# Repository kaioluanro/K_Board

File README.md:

# K_Board

Project 65% keyboard RGB custom, based in the QMK Firmware with uma display.

## Note

Project in development

## Features Hardware

- 256 GPIO digitais.
- Rotery Encode Switch.
- Display, Show menu options.

## Licença

[GPL3](https://choosealicense.com/licenses/gpl-3.0/)

## Autores

- [@kaioluanro](https://github.com/kaioluanro)

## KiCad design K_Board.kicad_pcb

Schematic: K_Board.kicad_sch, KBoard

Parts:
C1, C2, C3, C4, C10, C15, C16, C17, C18, C19, C20, C21, C22, C23, C24, C25, C26, C27, C28, C29, C30, C31, C32, C33, C34, C35, C36, C37, C38, C39, C40, C41, C42, C43, C44, C45, C46, C47, C48, C49, C50, C51, C52, C53, C54, C55, C56, C57, C58, C59, C60, C61, C62, C63, C64, C65, C66, C67, C68, C69, C70, C71, C72, C73, C74, C75, C76, C77, C78, C79, C80, C81, C82, C83, C84, C85, C86, C87, C88, C89, C90, C91, C102, C103, C104, C105, C106, C107, C108, C109, C110, C111, C112, C113, C114, C115, C116: 100n; C_0402_1005Metric; Manufacturer Part Number 0402F104Z160CT
C5: 10u; CP_EIA-3216-10_Kemet-I_Pad1.58x1.35mm_HandSolder; Manufacturer Part Number TAJA106K016RNJ
C6, C12, C14: 1u; C_0201_0603Metric; Manufacturer Part Number UMK107AB7105KA-T
C7: 10n; C_0402_1005Metric
C8, C9: 8p; C_0402_1005Metric
C11: 4.7u; C_0402_1005Metric
C13, C92, C97: 10u; C_0402_1005Metric; Manufacturer Part Number UMK325AB7106KM-T
C93: 15u; C_0402_1005Metric; Manufacturer Part Number UMK325AB7106KM-T
C94, C95, C99, C100: 1u; C_0805_2012Metric; Manufacturer Part Number CC0805KKX7R7BB105
C96: 2.2u; C_1206_3216Metric
C98: 4.7u; C_1206_3216Metric
C101: 0.1u; C_1206_3216Metric
D1, D7, D13, D19, D24, D29, D34, D40, D45, D50, D55, D61, D67, D70, D71, D83, D85, D86, D87, D88, D89, D90, D91, D92, D93, D94, D95, D96, D97, D98, D99, D100, D101, D102, D103, D104, D105, D106, D107, D108, D109, D110, D111, D112, D113, D114, D115, D116, D117, D118, D119, D120, D121, D122, D123, D124, D125, D126, D127, D128, D129, D130, D131, D132, D133, D134, D135, D136, D137, D138, D139, D140, D141, D162, D163, D164, D165, D166, D167, D168, D169, D170, D171, D172, D173, D174, D175, D176: WS2812B-Mini; LED_SK6812MINI_PLCC4_3.5x3.5mm_P1.75mm; Manufacturer Part Number WS2812B-Mini
D2, D3, D4, D5, D6, D8, D9, D10, D11, D12, D14, D15, D16, D17, D18, D20, D21, D22, D23, D25, D26, D27, D28, D30, D31, D32, D33, D35, D36, D37, D38, D39, D41, D42, D43, D44, D46, D47, D48, D49, D51, D52, D53, D54, D56, D57, D58, D59, D60, D62, D63, D64, D65, D66, D68, D69, D72, D73, D74, D75, D76, D77, D78, D79, D80, D81, D82, D142, D143, D146, D147, D148, D149, D150, D151, D152, D153, D154, D155, D156, D157, D158, D159, D160, D161: 1N4148W; D_SOD-123; Manufacturer Part Number 1N4148W
D84: ZRE B5819W-SL; D_SOD-123; Manufacturer Part Number B5819W-SL
D144, D145: 1N4148W; D_SOD-123
F1: mSMD110-16V; C_1812_4532Metric; Manufacturer Part Number mSMD110-16V
FB1: CBW201209U121T; L_0805_2012Metric; Manufacturer Part Number CBW201209U121T
J1: TYPE-C-31-M-12; USB_C_Receptacle_Hroparts_TYPE-C-31-M-12; Manufacturer Part Number TYPE-C-31-M-12
J2: Conn_01x04; PinHeader_1x4_P2.54mm_Angled
J3: Conns_I2C; SC-74-6_1.5x2.9mm_P0.95mm
J4: Conn_02x18_Counter_Clockwise; SMDIP-18_W7.62mm
J5: USB pins; PinHeader_1x4_P2.54mm_Angled
LED1, LED2, LED3, LED4, LED5, LED6, LED7, LED8, LED9, LED10: LED; LED_THT_2.54mm
Q1: 2N7002; SOT-23; Manufacturer Part Number 2N7002
Q2: AO3401A; SOT-23; Manufacturer Part Number Alpha & Omega Semicon
Q3, Q4: 2N7002; SOT-23
R1, R2: 4.7k; R_0402_1005Metric
R3, R55: 10k; R_0805_2012Metric
R4, R10, R11, R12, R13, R14, R15, R16, R17, R18, R19, R20, R21, R22, R23, R24, R25, R26, R27, R28, R29, R30, R31, R32, R33, R34, R35, R36, R37, R38, R39, R40, R41, R42, R43, R44, R45, R47, R48, R49, R50, R51, R52, R53, R54, R56, R57, R58, R59, R60, R61, R62, R63, R64, R65, R66, R67, R68, R69, R70, R71, R72, R73, R74, R75, R76, R77, R78, R79, R80, R81, R82, R83, R112, R113, R114, R115, R116, R117, R118, R119, R120, R121, R122, R123, R124, R125, R126: 5.1R; R_0805_2012Metric
R5: 0R; R_0402_1005Metric
R6, R7: 100k; R_0805_2012Metric
R8, R9: 5.1k; R_0805_2012Metric
R46: 1.5k; R_0402_1005Metric
R84, R85, R101, R102, R103, R104, R105: 4.7k; R_0805_2012Metric
R86, R87, R89, R90, R93, R94, R96, R97, R98, R99: 1k; R_0805_2012Metric; Manufacturer Part Number 0805W8F1001T5E
R88, R95: 100R; R_0402_1005Metric; Manufacturer Part Number 0402WGF1000TCE
R91, R92: 10k; R_0402_1005Metric; Manufacturer Part Number 0402WGF1002TCE
R100: 530k; R_0805_2012Metric
R106, R108, R110: 100R; R_0402_1005Metric
R107: 330k; R_0402_1005Metric
R109: 1M; R_0402_1005Metric
R111: 10K; R_0402_1005Metric
SW1: EC11E1544407; RotaryEncoder_Alps_EC11E-Switch_Vertical_H20mm; Manufacturer Part Number EC11E1544407
SW2, SW8, SW9, SW10, SW11, SW14, SW15, SW16, SW17, SW19, SW20, SW21, SW22, SW23, SW24, SW25, SW26, SW27, SW28, SW29, SW30, SW31, SW32, SW33, SW34, SW35, SW36, SW37, SW38, SW40, SW41, SW42, SW43, SW44, SW45, SW46, SW47, SW48, SW49, SW50, SW51, SW52, SW53, SW54, SW55, SW56, SW57, SW58, SW59, SW60, SW61, SW62, SW63, SW64, SW65, SW66, SW67, SW68, SW69, SW70, SW71, SW72, SW74, SW76, SW77, SW78, SW79, SW80, SW81, SW82, SW83, SW84: Mechanical_Switch; MX100
SW3: Mechanical_Switch; MX150
SW4, SW75: Mechanical_Switch; MX175
SW5, SW6, SW12, SW18: Mechanical_Switch; MX125
SW7: Mechanical_Switch; MX225
SW13: K2-1187SQ-A4SW-06; Manufacturer Part Number K2-1187SQ-A4SW-06
SW39: Mechanical_Switch; MX625R
SW73, SW85, SW86: Mechanical_Switch; MX200
U1: AT24C256C-SSHL-T; SOIC-8; Manufacturer Part Number AT24C256C-SSHL-T
U2: STM32F411CEU6; STM_UFQFPN-48_LQFP-48-1EP_7x7mm_P0.5mm_HandSoldering_Therma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; Manufacturer Part Number STM32F411
U3: SGM2007-3.3XN5/TR; SOT-23-5; Manufacturer Part Number SGM2007-3.3XN5/TR
U4: TXS0101DCKR; SOT-363_SC-70-6; Manufacturer Part Number TXS0101DCKR
U5, U6: PCF8575; VQFN-24-1EP_4x4mm_P0.5mm_EP2.45x2.45mm_ThermalVias
U7: 0.96'_display_OLED; 0.96 OLED Display
U8: USBLC6-2SC6; SOT-23-6; Manufacturer Part Number USBLC6-2SC6; LCSC Part Number C7519
X1: X6521WR-2x05H-C30D60; PinHeader_2x5_P2.54mm_Vertical_Staggered; Manufacturer Part Number X6521WR-2x05H-C30D60
X2: Conn_01x03; PinHeader_1x3_P2.54mm_Vertical
Y1: X1E0000210621; Crystal_SMD_3225-4Pin_3.2x2.5mm; Manufacturer Part Number 25MHz SMD Crystal Resonator 9pF 40Ω ±10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

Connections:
3V3: C1.2, C2.1, C3.1, C4.2, C5.1, C6.1, C7.1, C10.2, C14.1, C62.1, C94.2, C95.2, D84.2 (A), D144.1 (K), J2.2, J2.3, J2.4, J3.3, J3.4, J3.5, J3.6, R1.1, R2.1, R7.1, R46.1, R55.1, R84.1, R85.1, R101.2, R102.1, R103.1, R104.1, R105.1, SW13.1 (A), U1.8 (VCC), U2.1 (VBAT), U2.9 (VDDA/VREF+), U2.21 (B10), U2.24 (VDD), U2.29 (PA8), U2.36 (VDD), U2.39 (PB3), U2.40 (PB4), U2.48 (VDD), U3.5 (OUT), U4.1 (VCCA), U5.24 (VCC), U6.21 (A0), U6.24 (VCC), U7.5 (VCC), U7.8 (VCC), X1.7, X1.8
5V: C12.1, C63.2, D84.1 (K), F1.2, J5.1, Q2.2 (S), R4.2, R6.1, R10.2, R11.2, R12.2, R13.2, R14.2, R15.2, R16.2, R17.2, R18.2, R19.2, R20.2, R21.2, R22.2, R23.2, R24.2, R25.2, R26.2, R27.2, R28.2, R29.2, R30.2, R31.2, R32.2, R33.2, R34.2, R35.2, R36.2, R37.2, R38.2, R39.2, R40.2, R41.2, R42.2, R43.2, R44.2, R45.2, R47.2, R48.2, R49.2, R50.2, R51.2, R52.2, R53.2, R54.2, R56.2, R57.2, R58.2, R59.2, R60.2, R61.2, R62.2, R63.2, R64.2, R65.2, R66.2, R67.2, R68.2, R69.2, R70.2, R71.2, R72.2, R73.2, R74.2, R75.2, R76.2, R77.2, R78.2, R79.2, R80.2, R81.2, R82.2, R83.2, R92.2, R112.2, R113.2, R114.2, R115.2, R116.2, R117.2, R118.2, R119.2, R120.2, R121.2, R122.2, R123.2, R124.2, R125.2, R126.2, U3.1 (IN), U3.3 (EN), U4.6 (VCCB), X2.1; also elsewhere on the board
BACKLIGHT_3V3: R88.1, U2.16 (PA6)
BOOT0: C92.1, R107.2, R109.1, R111.2, U2.44 (BOOT0), X1.5
C1: SW2.1, SW3.1, SW4.1, SW5.1, SW6.1, SW19.1, U5.4 (P0)
C2: SW8.1, SW9.1, SW10.1, SW11.1, SW12.1, SW24.1, U5.5 (P1)
C3: SW14.1, SW15.1, SW16.1, SW17.1, SW18.1, SW29.1, U5.6 (P2)
C4: SW20.1, SW21.1, SW22.1, SW23.1, SW34.1, U5.7 (P3)
C5: SW25.1, SW26.1, SW27.1, SW28.1, SW40.1, U5.8 (P4)
C6: SW30.1, SW31.1, SW32.1, SW33.1, SW45.1, U5.9 (P5)
C7: SW35.1, SW36.1, SW37.1, SW38.1, SW39.1, SW50.1, U5.10 (P6)
C8: SW41.1, SW42.1, SW43.1, SW44.1, SW55.1, U5.11 (P7)
C9: SW46.1, SW47.1, SW48.1, SW49.1, SW61.1, U5.13 (P10)
C10: SW51.1, SW52.1, SW53.1, SW54.1, SW67.1, U5.14 (P11)
C11: SW56.1, SW57.1, SW58.1, SW59.1, SW60.1, SW70.1, U5.15 (P12)
C12: SW62.1, SW63.1, SW64.1, SW65.1, SW66.1, SW71.1, U5.16 (P13)
C13: SW68.1, SW69.1, SW72.1, SW74.1, SW83.1, SW84.1, U5.17 (P14)
C14: SW7.1, SW73.1, SW75.1, SW76.1, SW85.1, U5.18 (P15)
C15: SW1.S1, SW79.1, SW80.1, U5.19 (P16)
C16: SW77.1, SW78.1, SW81.1, SW82.1, SW86.1, U5.20 (P17)
DATA_BUS +: J1.A6 (D+), J1.B6 (D+), J5.2, U8.6 (I/O1); also elsewhere on the board
DATA_BUS -: J1.A7 (D-), J1.B7 (D-), J5.3, U8.4 (I/O2); also elsewhere on the board
DATA_USB +: R46.2, U2.33 (PA12/USB_FS_DP), U8.1 (I/O1)
DATA_USB -: U2.32 (PA11/USB_FS_DM), U8.3 (I/O2)
EEPROM_SCL: J3.1, R2.2, U1.6 (SCL), U2.42 (PB6/I2C1_SCL)
EEPROM_SDA: J3.2, R1.2, U1.5 (SDA), U2.43 (PB7/I2C1_SDA)
E_PA0-WKUP: J4.1, U2.10 (PA0-WKUP)
E_PA1: J4.2, U2.11 (PA1)
E_PA2: J4.3, U2.12 (PA2)
E_PA3: J4.4, U2.13 (PA3)
E_PA4: J4.5, U2.14 (PA4)
E_PA7: J4.6, U2.17 (PA7)
E_PA10: J4.7, U2.31 (PA10)
E_PA15: J4.8, U2.38 (PA15)
E_PB0: J4.9, U2.18 (PB0)
E_PB1: J4.10, U2.19 (PB1)
E_PB5: J4.11, U2.41 (PB5)
E_PB8: J4.12, U2.45 (PB8)
E_PB9: J4.13, U2.46 (PB9)
E_PB12: J4.14, U2.25 (PB12)
E_PB13: J4.15, U2.26 (PB13/SPI2_SCK)
E_PB14: J4.16, U2.27 (PB14)
E_PB15: J4.17, U2.28 (PB15/SPI2_MOSI)
E_PC13: J4.18, U2.2 (PC13)
E_S2: D143.2 (A), SW1.S2
Encode_A: C60.2, SW1.A, U2.4 (PC15_OSC32OUT)
Encode_B: C61.1, SW1.B, U2.3 (PC14_OSC32IN)
GND: C1.1, C2.2, C3.2, C4.1, C5.2, C6.2, C7.2, C8.2, C9.2, C10.1, C11.1, C12.2, C13.2, C14.2, C15.1, C16.1, C17.1, C18.1, C19.1, C20.1, C21.1, C22.1, C23.1, C24.1, C25.1, C26.1, C27.1, C28.1, C29.1, C30.1, C31.1, C32.1, C33.1, C34.1, C35.1, C36.1, C37.1, C38.1, C39.1, C40.1, C41.1, C42.1, C43.1, C44.1, C45.1, C46.1, C47.1, C48.1, C49.1, C50.1, C51.1, C52.1, C53.1, C54.1, C55.1, C56.1, C57.1, C58.1, C59.1, C60.1, C61.2, C62.2, C63.1, C64.1, C65.1, C66.1, C67.1, C68.1, C69.1, C70.1, C71.1, C72.1, C73.1, C74.1, C75.1, C76.1, C77.1, C78.1, C79.1, C80.1, C81.1, C82.1, C83.1, C84.1, C85.1, C86.1, C87.1, C88.1, C89.1, C90.1, C91.1, C92.2, C93.2, C94.1, C95.1, C96.2, C97.1, C98.2, C101.2, C102.1, C103.1, C104.1, C105.1, C106.1, C107.1, C108.1, C109.1, C110.1, C111.1, C112.1, C113.1, C114.1, C115.1, C116.1, D1.3 (VSS/GND), D7.3 (VSS/GND), D13.3 (VSS/GND), D19.3 (VSS/GND), D24.3 (VSS/GND), D29.3 (VSS/GND), D34.3 (VSS/GND), D40.3 (VSS/GND), D45.3 (VSS/GND), D50.3 (VSS/GND), D55.3 (VSS/GND), D61.3 (VSS/GND), D67.3 (VSS/GND), D70.3 (VSS/GND), D71.3 (VSS/GND), D83.3 (VSS/GND), D85.3 (VSS/GND), D86.3 (VSS/GND), D87.3 (VSS/GND), D88.3 (VSS/GND), D89.3 (VSS/GND), D90.3 (VSS/GND), D91.3 (VSS/GND), D92.3 (VSS/GND), D93.3 (VSS/GND), D94.3 (VSS/GND), D95.3 (VSS/GND), D96.3 (VSS/GND), D97.3 (VSS/GND), D98.3 (VSS/GND), D99.3 (VSS/GND), D100.3 (VSS/GND), D101.3 (VSS/GND), D102.3 (VSS/GND), D103.3 (VSS/GND), D104.3 (VSS/GND), D105.3 (VSS/GND), D106.3 (VSS/GND), D107.3 (VSS/GND), D108.3 (VSS/GND), D109.3 (VSS/GND), D110.3 (VSS/GND), D111.3 (VSS/GND), D112.3 (VSS/GND), D113.3 (VSS/GND), D114.3 (VSS/GND), D115.3 (VSS/GND), D116.3 (VSS/GND), D117.3 (VSS/GND), D118.3 (VSS/GND), D119.3 (VSS/GND), D120.3 (VSS/GND), D121.3 (VSS/GND), D122.3 (VSS/GND), D123.3 (VSS/GND), D124.3 (VSS/GND), D125.3 (VSS/GND), D126.3 (VSS/GND), D127.3 (VSS/GND), D128.3 (VSS/GND), D129.3 (VSS/GND), D130.3 (VSS/GND), D131.3 (VSS/GND), D132.3 (VSS/GND), D133.3 (VSS/GND), D134.3 (VSS/GND), D135.3 (VSS/GND), D136.3 (VSS/GND), D137.3 (VSS/GND), D138.3 (VSS/GND), D139.3 (VSS/GND), D140.3 (VSS/GND), D141.3 (VSS/GND), D162.3 (VSS/GND), D163.3 (VSS/GND), D164.3 (VSS/GND), D165.3 (VSS/GND), D166.3 (VSS/GND), D167.3 (VSS/GND), D168.3 (VSS/GND), D169.3 (VSS/GND), D170.3 (VSS/GND), D171.3 (VSS/GND), D172.3 (VSS/GND), D173.3 (VSS/GND), D174.3 (VSS/GND), D175.3 (VSS/GND), D176.3 (VSS/GND), FB1.2, J1.A1 (GND), J1.B1 (GND), J2.1, J5.4, LED3.K, LED4.K, LED5.K, LED6.K, LED7.K, LED8.K, LED9.K, LED10.K, Q1.2 (S), Q3.2 (S), Q4.2 (S), R3.2, R6.2, R7.2, R8.2, R9.2, R86.2, R87.2, R91.1, R100.2, R109.2, SW1.C, U1.1 (A0), U1.2 (A1), U1.3 (A2), U1.4 (GND), U1.7 (WP), U2.8 (VSSA), U2.23 (VSS), U2.35 (VSS), U2.47 (VSS), U3.2 (GND), U4.2 (GND), U5.2 (A1), U5.3 (A2), U5.12 (GND), U5.21 (A0), U6.2 (A1), U6.3 (A2), U6.12 (GND), U7.7 (VSS), U8.2 (GND), X1.3, X1.4, X1.10, X2.3, Y1.2, Y1.4; also elsewhere on the board
GNDPWR: FB1.1, J1.S1 (SHIELD)
L1: D146.1 (K), D147.1 (K), D148.1 (K), D149.1 (K), D150.1 (K), D151.1 (K), D152.1 (K), D153.1 (K), D154.1 (K), D155.1 (K), D156.1 (K), D157.1 (K), D158.1 (K), D160.1 (K), U6.4 (P0)
L2: D2.1 (K), D8.1 (K), D14.1 (K), D20.1 (K), D25.1 (K), D30.1 (K), D35.1 (K), D41.1 (K), D46.1 (K), D51.1 (K), D56.1 (K), D62.1 (K), D68.1 (K), D73.1 (K), D143.1 (K), D161.1 (K), U6.5 (P1)
L3: D3.1 (K), D9.1 (K), D15.1 (K), D21.1 (K), D26.1 (K), D31.1 (K), D36.1 (K), D42.1 (K), D47.1 (K), D52.1 (K), D57.1 (K), D63.1 (K), D69.1 (K), D77.1 (K), U6.6 (P2)
L4: D4.1 (K), D10.1 (K), D16.1 (K), D22.1 (K), D27.1 (K), D32.1 (K), D37.1 (K), D43.1 (K), D48.1 (K), D53.1 (K), D58.1 (K), D64.1 (K), D74.1 (K), D78.1 (K), D142.1 (K), U6.7 (P3)
L5: D5.1 (K), D11.1 (K), D17.1 (K), D23.1 (K), D28.1 (K), D33.1 (K), D38.1 (K), D44.1 (K), D49.1 (K), D54.1 (K), D59.1 (K), D65.1 (K), D75.1 (K), D79.1 (K), D81.1 (K), D159.1 (K), U6.8 (P4)
L6: D6.1 (K), D12.1 (K), D18.1 (K), D39.1 (K), D60.1 (K), D66.1 (K), D72.1 (K), D76.1 (K), D80.1 (K), D82.1 (K), U6.9 (P5)
NRST: C93.1, R110.2, U2.7 (NRST), X1.9
unnamed: C11.2, U2.22 (VCAP_1)
unnamed: C13.1, U3.4 (BP/FB)
unnamed: C15.2, D1.1 (VDD), R4.1
unnamed: C16.2, D7.1 (VDD), R10.1
unnamed: C17.2, D13.1 (VDD), R11.1
unnamed: C18.2, D19.1 (VDD), R12.1
unnamed: C19.2, D24.1 (VDD), R13.1
unnamed: C20.2, D29.1 (VDD), R14.1
unnamed: C21.2, D34.1 (VDD), R15.1
unnamed: C22.2, D40.1 (VDD), R16.1
unnamed: C23.2, D45.1 (VDD), R17.1
unnamed: C24.2, D50.1 (VDD), R18.1
unnamed: C25.2, D55.1 (VDD), R19.1
unnamed: C26.2, D61.1 (VDD), R20.1
unnamed: C27.2, D67.1 (VDD), R21.1
unnamed: C28.2, D70.1 (VDD), R22.1
unnamed: C29.2, D71.1 (VDD), R23.1
unnamed: C30.2, D83.1 (VDD), R24.1
unnamed: C31.2, D85.1 (VDD), R25.1
unnamed: C32.2, D86.1 (VDD), R26.1
unnamed: C33.2, D87.1 (VDD), R27.1
unnamed: C34.2, D88.1 (VDD), R28.1
unnamed: C35.2, D89.1 (VDD), R29.1
unnamed: C36.2, D90.1 (VDD), R30.1
unnamed: C37.2, D91.1 (VDD), R31.1
unnamed: C38.2, D92.1 (VDD), R32.1
unnamed: C39.2, D93.1 (VDD), R33.1
unnamed: C40.2, D94.1 (VDD), R34.1
unnamed: C41.2, D95.1 (VDD), R35.1
unnamed: C42.2, D96.1 (VDD), R36.1
unnamed: C43.2, D97.1 (VDD), R37.1
unnamed: C44.2, D98.1 (VDD), R38.1
unnamed: C45.2, D99.1 (VDD), R39.1
unnamed: C46.2, D100.1 (VDD), R40.1
unnamed: C47.2, D101.1 (VDD), R41.1
unnamed: C48.2, D102.1 (VDD), R42.1
unnamed: C49.2, D103.1 (VDD), R43.1
unnamed: C50.2, D104.1 (VDD), R44.1
unnamed: C51.2, D105.1 (VDD), R45.1
unnamed: C52.2, D106.1 (VDD), R47.1
unnamed: C53.2, D107.1 (VDD), R48.1
unnamed: C54.2, D108.1 (VDD), R49.1
unnamed: C55.2, D109.1 (VDD), R50.1
unnamed: C56.2, D110.1 (VDD), R51.1
unnamed: C57.2, D111.1 (VDD), R52.1
unnamed: C58.2, D112.1 (VDD), R53.1
unnamed: C59.2, D113.1 (VDD), R54.1
unnamed: C64.2, D114.1 (VDD), R56.1
unnamed: C65.2, D115.1 (VDD), R57.1
unnamed: C66.2, D116.1 (VDD), R58.1
unnamed: C67.2, D117.1 (VDD), R59.1
unnamed: C68.2, D118.1 (VDD), R60.1
unnamed: C69.2, D119.1 (VDD), R61.1
unnamed: C70.2, D120.1 (VDD), R62.1
unnamed: C71.2, D121.1 (VDD), R63.1
unnamed: C72.2, D122.1 (VDD), R64.1
unnamed: C73.2, D123.1 (VDD), R65.1
unnamed: C74.2, D124.1 (VDD), R66.1
unnamed: C75.2, D125.1 (VDD), R67.1
unnamed: C76.2, D126.1 (VDD), R68.1
unnamed: C77.2, D127.1 (VDD), R69.1
unnamed: C78.2, D128.1 (VDD), R70.1
unnamed: C79.2, D129.1 (VDD), R71.1
unnamed: C80.2, D130.1 (VDD), R72.1
unnamed: C81.2, D131.1 (VDD), R73.1
unnamed: C82.2, D132.1 (VDD), R74.1
unnamed: C83.2, D133.1 (VDD), R75.1
unnamed: C84.2, D134.1 (VDD), R76.1
unnamed: C85.2, D135.1 (VDD), R77.1
unnamed: C86.2, D136.1 (VDD), R78.1
unnamed: C87.2, D137.1 (VDD), R79.1
unnamed: C88.2, D138.1 (VDD), R80.1
unnamed: C89.2, D139.1 (VDD), R81.1
unnamed: C90.2, D140.1 (VDD), R82.1
unnamed: C91.2, D141.1 (VDD), R83.1
unnamed: C96.1, U7.13 (VCOMF)
unnamed: C99.1, U7.1 (C2P)
unnamed: C99.2, U7.2 (C2N)
unnamed: C100.1, U7.3 (C1P)
unnamed: C100.2, U7.4 (C1N)
unnamed: C98.1, C101.1, U7.14 (VCC)
unnamed: C102.2, D162.1 (VDD), R112.1
unnamed: C103.2, D163.1 (VDD), R113.1
unnamed: C104.2, D164.1 (VDD), R114.1
unnamed: C105.2, D165.1 (VDD), R115.1
unnamed: C106.2, D166.1 (VDD), R116.1
unnamed: C107.2, D167.1 (VDD), R117.1
unnamed: C108.2, D168.1 (VDD), R118.1
unnamed: C109.2, D169.1 (VDD), R119.1
unnamed: C110.2, D170.1 (VDD), R120.1
unnamed: C111.2, D171.1 (VDD), R121.1
unnamed: C112.2, D172.1 (VDD), R122.1
unnamed: C113.2, D173.1 (VDD), R123.1
unnamed: C114.2, D174.1 (VDD), R124.1
unnamed: C115.2, D175.1 (VDD), R125.1
unnamed: C116.2, D176.1 (VDD), R126.1
unnamed: D1.2 (DOUT), D29.4 (DIN)
unnamed: D1.4 (DIN), D140.2 (DOUT)
unnamed: D2.2 (A), SW2.2
unnamed: D3.2 (A), SW3.2
unnamed: D4.2 (A), SW4.2
unnamed: D5.2 (A), SW5.2
unnamed: D6.2 (A), SW6.2
unnamed: D8.2 (A), SW8.2
unnamed: D9.2 (A), SW9.2
unnamed: D10.2 (A), SW10.2
unnamed: D11.2 (A), SW11.2
unnamed: D12.2 (A), SW12.2
unnamed: D13.2 (DOUT), D40.4 (DIN)
unnamed: D13.4 (DIN), D136.2 (DOUT)
unnamed: D14.2 (A), SW14.2
unnamed: D15.2 (A), SW15.2
unnamed: D16.2 (A), SW16.2
unnamed: D17.2 (A), SW17.2
unnamed: D18.2 (A), SW18.2
unnamed: D19.2 (DOUT), D45.4 (DIN)
unnamed: D20.2 (A), SW20.2
unnamed: D21.2 (A), SW21.2
unnamed: D22.2 (A), SW22.2
unnamed: D23.2 (A), SW23.2
unnamed: D24.2 (DOUT), D50.4 (DIN)
unnamed: D25.2 (A), SW25.2
unnamed: D26.2 (A), SW26.2
unnamed: D27.2 (A), SW27.2
unnamed: D28.2 (A), SW28.2
unnamed: D29.2 (DOUT), D55.4 (DIN)
unnamed: D30.2 (A), SW30.2
unnamed: D31.2 (A), SW31.2
unnamed: D32.2 (A), SW32.2
unnamed: D33.2 (A), SW33.2
unnamed: D34.2 (DOUT), D61.4 (DIN)
unnamed: D7.2 (DOUT), D34.4 (DIN)
unnamed: D35.2 (A), SW35.2
unnamed: D36.2 (A), SW36.2
unnamed: D37.2 (A), SW37.2
unnamed: D38.2 (A), SW38.2
unnamed: D39.2 (A), SW39.2
unnamed: D40.2 (DOUT), D67.4 (DIN)
unnamed: D41.2 (A), SW41.2
unnamed: D42.2 (A), SW42.2
unnamed: D43.2 (A), SW43.2
unnamed: D44.2 (A), SW44.2
unnamed: D45.2 (DOUT), D70.4 (DIN)
unnamed: D46.2 (A), SW46.2
unnamed: D47.2 (A), SW47.2
unnamed: D48.2 (A), SW48.2
unnamed: D49.2 (A), SW49.2
unnamed: D50.2 (DOUT), D71.4 (DIN)
unnamed: D51.2 (A), SW51.2
unnamed: D52.2 (A), SW52.2
unnamed: D53.2 (A), SW53.2
unnamed: D54.2 (A), SW54.2
unnamed: D55.2 (DOUT), D83.4 (DIN)
unnamed: D56.2 (A), SW56.2
unnamed: D57.2 (A), SW57.2
unnamed: D58.2 (A), SW58.2
unnamed: D59.2 (A), SW59.2
unnamed: D60.2 (A), SW60.2
unnamed: D61.2 (DOUT), D85.4 (DIN)
unnamed: D62.2 (A), SW62.2
unnamed: D63.2 (A), SW63.2
unnamed: D64.2 (A), SW64.2
unnamed: D65.2 (A), SW65.2
unnamed: D66.2 (A), SW66.2
unnamed: D67.2 (DOUT), D86.4 (DIN)
unnamed: D68.2 (A), SW68.2
unnamed: D69.2 (A), SW69.2
unnamed: D70.2 (DOUT), D87.4 (DIN)
unnamed: D71.2 (DOUT), D96.4 (DIN)
unnamed: D72.2 (A), SW72.2
unnamed: D73.2 (A), SW73.2
unnamed: D74.2 (A), SW74.2
unnamed: D75.2 (A), SW75.2
unnamed: D76.2 (A), SW76.2
unnamed: D77.2 (A), SW77.2
unnamed: D78.2 (A), SW78.2
unnamed: D79.2 (A), SW79.2
unnamed: D80.2 (A), SW80.2
unnamed: D81.2 (A), SW81.2
unnamed: D82.2 (A), SW82.2
unnamed: D83.2 (DOUT), D88.4 (DIN)
unnamed: D85.2 (DOUT), D89.4 (DIN)
unnamed: D86.2 (DOUT), D90.4 (DIN)
unnamed: D87.2 (DOUT), D91.4 (DIN)
unnamed: D88.2 (DOUT), D92.4 (DIN)
unnamed: D89.2 (DOUT), D93.4 (DIN)
unnamed: D90.2 (DOUT), D94.4 (DIN)
unnamed: D91.2 (DOUT), D95.4 (DIN)
unnamed: D92.2 (DOUT), D97.4 (DIN)
unnamed: D93.2 (DOUT), D98.4 (DIN)
unnamed: D94.2 (DOUT), D99.4 (DIN)
unnamed: D100.2 (DOUT), D104.4 (DIN)
unnamed: D95.2 (DOUT), D100.4 (DIN)
unnamed: D101.2 (DOUT), D106.4 (DIN)
unnamed: D97.2 (DOUT), D101.4 (DIN)
unnamed: D102.2 (DOUT), D107.4 (DIN)
unnamed: D98.2 (DOUT), D102.4 (DIN)
unnamed: D103.2 (DOUT), D108.4 (DIN)
unnamed: D99.2 (DOUT), D103.4 (DIN)
unnamed: D104.2 (DOUT), D109.4 (DIN)
unnamed: D105.2 (DOUT), D118.4 (DIN)
unnamed: D96.2 (DOUT), D105.4 (DIN)
unnamed: D106.2 (DOUT), D110.4 (DIN)
unnamed: D107.2 (DOUT), D111.4 (DIN)
unnamed: D108.2 (DOUT), D112.4 (DIN)
unnamed: D109.2 (DOUT), D113.4 (DIN)
unnamed: D110.2 (DOUT), D114.4 (DIN)
unnamed: D111.2 (DOUT), D115.4 (DIN)
unnamed: D112.2 (DOUT), D116.4 (DIN)
unnamed: D113.2 (DOUT), D117.4 (DIN)
unnamed: D114.2 (DOUT), D119.4 (DIN)
unnamed: D115.2 (DOUT), D120.4 (DIN)
unnamed: D116.2 (DOUT), D121.4 (DIN)
unnamed: D117.2 (DOUT), D122.4 (DIN)
unnamed: D118.2 (DOUT), D123.4 (DIN)
unnamed: D119.2 (DOUT), D124.4 (DIN)
unnamed: D120.2 (DOUT), D125.4 (DIN)
unnamed: D121.2 (DOUT), D129.4 (DIN)
unnamed: D122.2 (DOUT), D126.4 (DIN)
unnamed: D123.2 (DOUT), D127.4 (DIN)
unnamed: D124.2 (DOUT), D128.4 (DIN)
unnamed: D126.2 (DOUT), D176.4 (DIN)
unnamed: D127.2 (DOUT), D131.4 (DIN)
unnamed: D128.2 (DOUT), D135.4 (DIN)
unnamed: D130.2 (DOUT), D137.4 (DIN)
unnamed: D129.2 (DOUT), D130.4 (DIN)
unnamed: D131.2 (DOUT), D133.4 (DIN)
unnamed: D132.2 (DOUT), D138.4 (DIN)
unnamed: D132.4 (DIN), D176.2 (DOUT)
unnamed: D133.2 (DOUT), D139.4 (DIN)
unnamed: D134.2 (DOUT), D140.4 (DIN)
unnamed: D134.4 (DIN), D175.2 (DOUT)
unnamed: D135.2 (DOUT), D141.4 (DIN)
unnamed: D125.2 (DOUT), D136.4 (DIN)
unnamed: D19.4 (DIN), D137.2 (DOUT)
unnamed: D24.4 (DIN), D138.2 (DOUT)
unnamed: D7.4 (DIN), D141.2 (DOUT)
unnamed: D142.2 (A), SW7.2
unnamed: D145.1 (K), R107.1
unnamed: D145.2 (A), R106.1, SW13.2 (B)
unnamed: D146.2 (A), SW19.2
unnamed: D147.2 (A), SW24.2
unnamed: D148.2 (A), SW29.2
unnamed: D149.2 (A), SW34.2
unnamed: D150.2 (A), SW40.2
unnamed: D151.2 (A), SW45.2
unnamed: D152.2 (A), SW50.2
unnamed: D153.2 (A), SW55.2
unnamed: D154.2 (A), SW61.2
unnamed: D155.2 (A), SW67.2
unnamed: D156.2 (A), SW70.2
unnamed: D157.2 (A), SW71.2
unnamed: D158.2 (A), SW83.2
unnamed: D159.2 (A), SW84.2
unnamed: D160.2 (A), SW85.2
unnamed: D161.2 (A), SW86.2
unnamed: D162.2 (DOUT), D163.4 (DIN)
unnamed: D163.2 (DOUT), D164.4 (DIN)
unnamed: D164.2 (DOUT), D165.4 (DIN)
unnamed: D165.2 (DOUT), D166.4 (DIN)
unnamed: D166.2 (DOUT), D167.4 (DIN)
unnamed: D167.2 (DOUT), D168.4 (DIN)
unnamed: D168.2 (DOUT), D169.4 (DIN)
unnamed: D169.2 (DOUT), D170.4 (DIN)
unnamed: D170.2 (DOUT), D171.4 (DIN)
unnamed: D171.2 (DOUT), D172.4 (DIN)
unnamed: D172.2 (DOUT), D173.4 (DIN)
unnamed: D173.2 (DOUT), D174.4 (DIN)
unnamed: D174.2 (DOUT), D175.4 (DIN)
unnamed 325: J1.A5 (CC1), R8.1; also elsewhere on the board
unnamed 326: J1.B5 (CC2), R9.1; also elsewhere on the board
unnamed: LED1.A, LED2.A, Q2.3 (D), R89.1, R90.1, R93.1, R94.1, R96.1, R97.1, R98.1, R99.1
unnamed: LED1.K, R86.1
unnamed: LED2.K, R87.1
unnamed: LED3.A, R89.2
unnamed: LED4.A, R90.2
unnamed: LED5.A, R93.2
unnamed: LED6.A, R94.2
unnamed: LED7.A, R96.2
unnamed: LED8.A, R97.2
unnamed: LED9.A, R98.2
unnamed: LED10.A, R99.2
unnamed: Q1.1 (G), R88.2, R91.2
unnamed: Q1.3 (D), R92.1, R95.2
unnamed: Q2.1 (G), R95.1
unnamed: Q3.1 (G), R106.2
unnamed: Q3.3 (D), R108.1, R110.1
unnamed: Q4.1 (G), R108.2
unnamed: Q4.3 (D), R111.1
unnamed: R5.2, U2.30 (PA9/USB_FS_VBUS)
unnamed: R55.2, U4.5 (OE)
unnamed: R84.2, U5.22 (SCL)
unnamed: R85.2, U5.23 (SDA)
unnamed: R100.1, U7.12 (IREF)
unnamed: R102.2, U7.10 (SCL)
unnamed: R103.2, U7.11 (SDA)
unnamed: R104.2, U6.22 (SCL)
unnamed: R105.2, U6.23 (SDA)
PB2/BOOT1: R3.1, U2.20 (PB2), X1.6
RESET_OLED: C97.2, D144.2 (A), R101.1, U7.9 (REF)
RGB_3V3: U2.15 (PA5), U4.3 (A)
RGB_5V: D162.4 (DIN), U4.4 (B)
RGB_OUT_5V: D139.2 (DOUT), X2.2
SWCLK: U2.37 (PA14/SWCLK), X1.2
SWDIO: U2.34 (PA13/SWDIO), X1.1
VBUS: F1.1, J1.A4 (VBUS), J1.B4 (VBUS), R5.1, U8.5 (VBUS); also elsewhere on the board
XTAL_IN: C9.1, U2.5 (PH0_OSCIN), Y1.3
XTAL_OUT: C8.1, U2.6 (PH1_OSCOUT), Y1.1

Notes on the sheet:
BlackLigth
RGB_Encode
*Total the 256 GPIO digital, in one I2C output .
OLED
Grid LEDs
Spooky pin (*)
*Read Address: 67(Decimal) or 43(hexadecimal) *White Address: 66(Decimal) or 42(hexadecimal)
USB
Grid Switch
(*) "Spooky pins": on STM32F4x1, pins A9 and B2 cannot be used for switch matrix: - A9 is meant to be used as a VBUS sensing. It has a undocumented internal pulldown resistor; - B2 is used as BOOT1 during bootup, so it needs an external pulldown for successful bootup
POWER
EXPENDER GPIO
MCU
Encode_Switch
USB ESD
*Read Address: 65(Decimal) or 41(hexadecimal) *Write Address: 64(Decimal) or 40(hexadecimal)
EEPROM
HARD RESET
Controller RGB
RotaryEncode_SW1
(**) PA9 jumper: a solderable jumper used to tie PA9 to VBUS. It is disconnected by default, hence PA9 is left floating

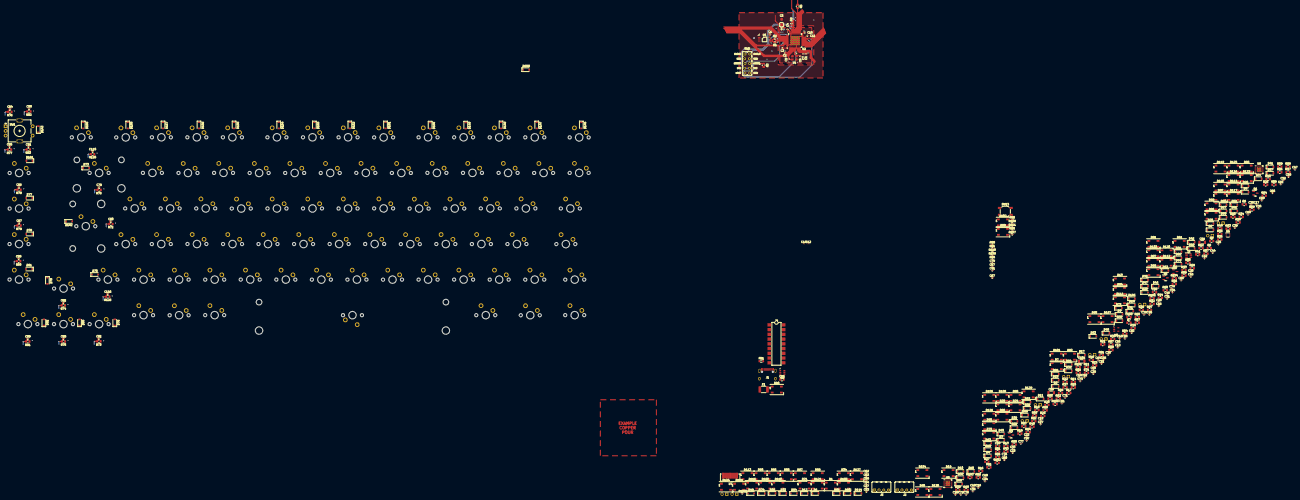
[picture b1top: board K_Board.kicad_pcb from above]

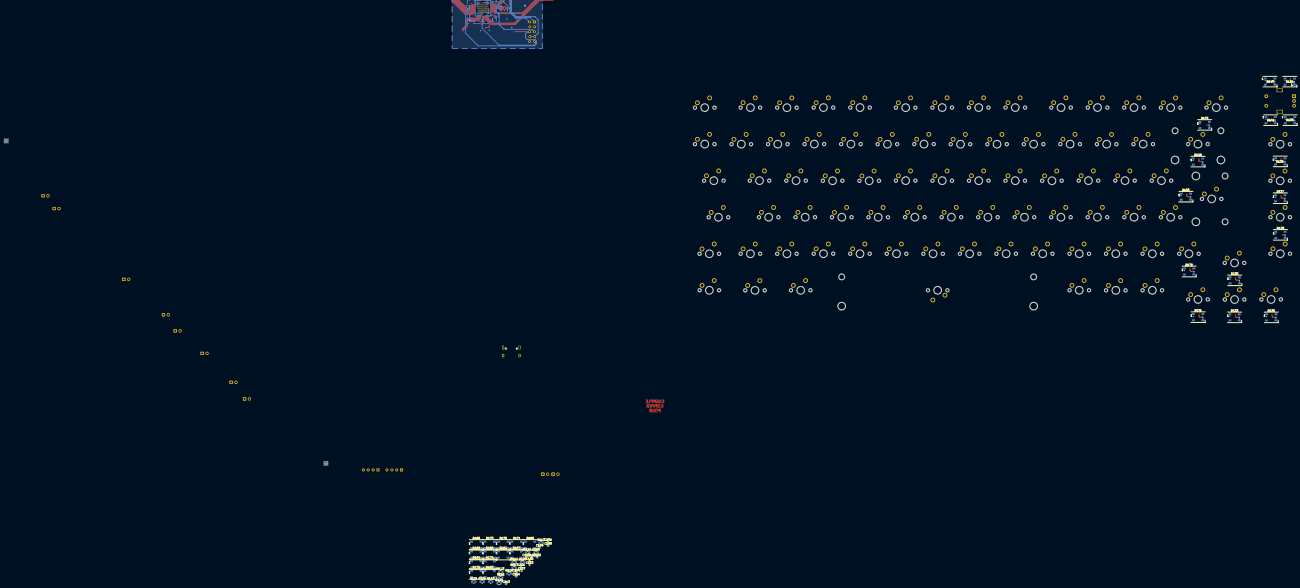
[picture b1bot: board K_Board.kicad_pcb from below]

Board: 2 copper layers, 535 parts (54 on the bottom side), 362 nets.

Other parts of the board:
F?: mSMD110-16V; C_1812_4532Metric
J?: TYPE-C-31-M-12; USB_C_Receptacle_Hroparts_TYPE-C-31-M-12

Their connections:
5V: F?.2; also elsewhere on the board
DATA_BUS +: J?.A6 (D+), J?.B6 (D+); also elsewhere on the board
DATA_BUS -: J?.A7 (D-), J?.B7 (D-); also elsewhere on the board
GND: J?.A1 (GND), J?.B1 (GND); also elsewhere on the board
unnamed 325: J?.A5 (CC1); also elsewhere on the board
unnamed 326: J?.B5 (CC2); also elsewhere on the board
VBUS: F?.1, J?.A4 (VBUS), J?.B4 (VBUS); also elsewhere on the board

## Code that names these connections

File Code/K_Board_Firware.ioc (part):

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Mcu.Name=STM32F411C(C-E)Ux
Mcu.Package=UFQFPN48
Mcu.UserName=STM32F411CEUx
PA11.Mode=Device_Only
PA11.Signal=USB_OTG_FS_DM
PA12.Mode=Device_Only
PA12.Signal=USB_OTG_FS_DP
PA5.GPIOParameters=GPIO_Label
PA5.GPIO_Label=RGB_LED_TIMCH1
PA5.Signal=S_TIM2_CH1_ETR
PA6.GPIOParameters=GPIO_Label
PA6.GPIO_Label=BACKLIGTH_CM
PA6.Signal=GPIO_Output
PA8.GPIOParameters=GPIO_Label
PA8.GPIO_Label=OLED_SCL
PA8.Mode=I2C
PA8.Signal=I2C3_SCL
PB10.GPIOParameters=GPIO_Label
PB10.GPIO_Label=EXT_GPIO_SCL
PB10.Mode=I2C
PB10.Signal=I2C2_SCL
PB3.GPIOParameters=GPIO_Label
PB3.GPIO_Label=EXT_GPIO_SDA
PB3.Mode=I2C
PB3.Signal=I2C2_SDA
PB4.GPIOParameters=GPIO_Label
PB4.GPIO_Label=OLED_SDA
PB4.Mode=I2C
PB4.Signal=I2C3_SDA
PB6.GPIOParameters=GPIO_Label
PB6.GPIO_Label=EEPROM_SCL
PB6.Mode=I2C
PB6.Signal=I2C1_SCL
PB7.GPIOParameters=GPIO_Label
PB7.GPIO_Label=EEPROM_SDA
PB7.Mode=I2C
PB7.Signal=I2C1_SDA
PC14-OSC32_IN.GPIOParameters=GPIO_Label
PC14-OSC32_IN.GPIO_Label=ENCODE_S_B
PC14-OSC32_IN.Signal=GPIO_Analog
PC15-OSC32_OUT.GPIOParameters=GPIO_Label
PC15-OSC32_OUT.GPIO_Label=ENCODE_S_A
PC15-OSC32_OUT.Signal=GPIO_Analog
RCC.HSE_VALUE=25000000
RCC.SYSCLKFreq_VALUE=16000000
board=custom

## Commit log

2022-09-02 02092022
